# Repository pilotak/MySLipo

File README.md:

# MySensors Li-po/USB powered wirelles node

PCB size as 18500 Li-po battery board with ATmega328p with integrated USB charger and battery protection IC. Supports ATSHA204A CryptoAuth chip, DS18B20 temperature IC and Meder reed switch.

### Power consumption
* sleep: 58.1uA
* wakeup: 18.2mA

### Supported radios:
* NRF24L01 SMD
* NRF24L01+LNA+PA SMD

### Pins used:
* D2 = reed switch 1
* D3 = reed switch 2
* D4 = 1-Wire bus with R2 pull-up to D5
* D5 = 1-Wire supply
* D7 = LED indication
* D9 = CE pin
* D10 = CSN
* SPI = radios
* A2 = ATSHA204A
* A7 = battery monitor

## PCB top view

## PCB bottom view

### ATmega328p fuses
- **HIGH:** DA
- **LOW:** E2
- **EXTENDED:** 06

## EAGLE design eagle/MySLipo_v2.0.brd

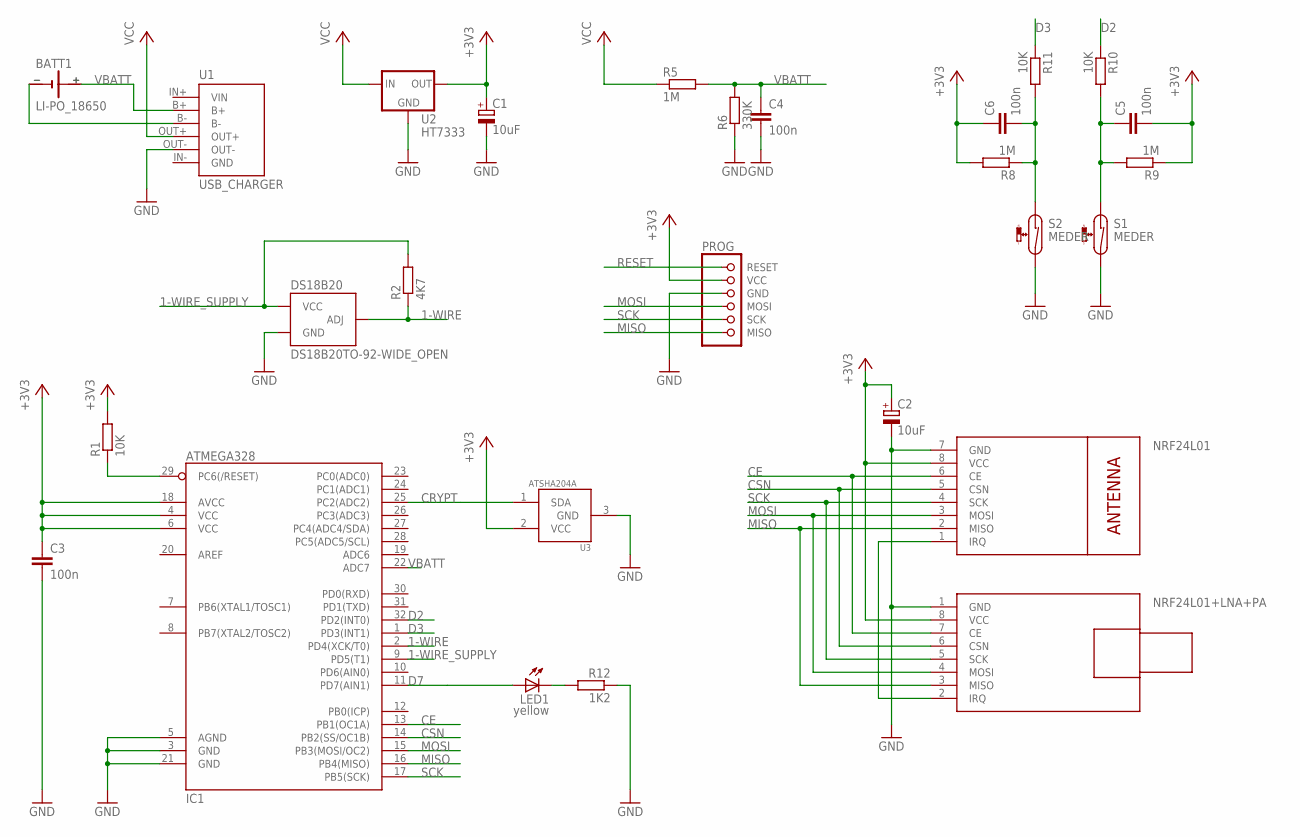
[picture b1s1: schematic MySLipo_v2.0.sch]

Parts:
BATT1: LI-PO_18650; 18650_HOLDER
C1, C2: 10uF; SMC_A
C3, C4, C5, C6: 100n; C0805
DS18B20: DS18B20TO-92-WIDE_OPEN; TO-92-WIDE_OPEN
IC1: ATMEGA328; TQFP32-08
LED1: yellow; LED_0805
NRF24L01: WIRELESS-NRF24L01SMD2; WIRELESS-NRF24L01-SMD-2
NRF24L01+LNA+PA: WIRELESS-NRF24L01-PA-EXTSMD; WIRELESS-NRF24L01-PA-SMD
PROG: PROG
R1, R10, R11: 10K; R0805
R2: 4K7; R0805
R5, R8, R9: 1M; R0805
R6: 330K; R0805
R12: 1K2; R0805
S1, S2: MEDER; 15X
U1: USB_CHARGER
U2: HT7333; SOT89
U3: ATSHA204A; SOT23-3

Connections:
1-WIRE: DS18B20.G (ADJ), IC1.2 (PD4(XCK/T0)), R2.1
1-WIRE_SUPPLY: DS18B20.S (VCC), IC1.9 (PD5(T1)), R2.2
+3V3: C1.+, C2.+, C3.1, C5.2, C6.1, IC1.4 (VCC), IC1.6 (VCC), IC1.18 (AVCC), NRF24L01.8 (VCC), NRF24L01+LNA+PA.8 (VCC), PROG.2 (VCC), R1.2, R8.2, R9.1, U2.3 (OUT), U3.2 (VCC)
CE: IC1.13 (PB1(OC1A)), NRF24L01.6 (CE), NRF24L01+LNA+PA.7 (CE)
CRYPT: IC1.25 (PC2(ADC2)), U3.1 (SDA)
CSN: IC1.14 (PB2(SS/OC1B)), NRF24L01.5 (CSN), NRF24L01+LNA+PA.6 (CSN)
D2: IC1.32 (PD2(INT0)), R10.1
D3: IC1.1 (PD3(INT1)), R11.1
D7: IC1.11 (PD7(AIN1)), LED1.1 (A)
GND: C1.-, C2.-, C3.2, C4.2, DS18B20.D (GND), IC1.3 (GND), IC1.5 (AGND), IC1.21 (GND), NRF24L01.7 (GND), NRF24L01+LNA+PA.1 (GND), PROG.3 (GND), R6.1, R12.1, S1.P$2 (2), S2.P$2 (2), U1.OUT-, U2.1 (GND), U3.3 (GND)
MISO: IC1.16 (PB4(MISO)), NRF24L01.2 (MISO), NRF24L01+LNA+PA.3 (MISO), PROG.6 (MISO)
MOSI: IC1.15 (PB3(MOSI/OC2)), NRF24L01.3 (MOSI), NRF24L01+LNA+PA.4 (MOSI), PROG.4 (MOSI)
unnamed: NRF24L01.1 (IRQ), NRF24L01+LNA+PA.2 (IRQ)
unnamed: C5.1, R9.2, R10.2, S1.P$1 (1)
unnamed: C6.2, R8.1, R11.2, S2.P$1 (1)
unnamed: BATT1.-, U1.B-
unnamed: LED1.2 (C), R12.2
RESET: IC1.29 (PC6(/RESET)), PROG.1 (RESET), R1.1
SCK: IC1.17 (PB5(SCK)), NRF24L01.4 (SCK), NRF24L01+LNA+PA.5 (SCK), PROG.5 (SCK)
VCC: R5.1, U1.OUT+, U2.2 (IN)

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
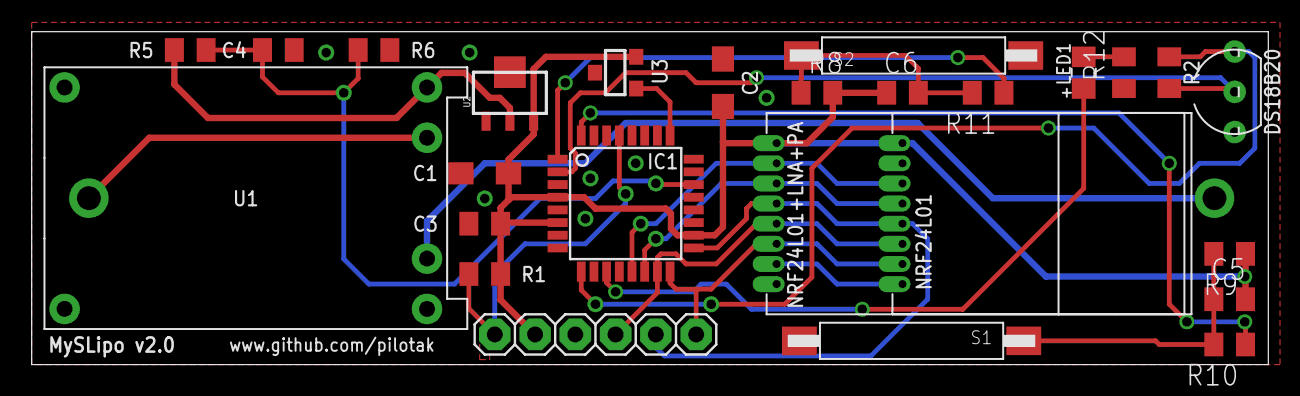
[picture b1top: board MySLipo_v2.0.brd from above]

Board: 2 copper layers, 78.0 x 21.0 mm, 27 parts (1 on the bottom side), 22 nets.

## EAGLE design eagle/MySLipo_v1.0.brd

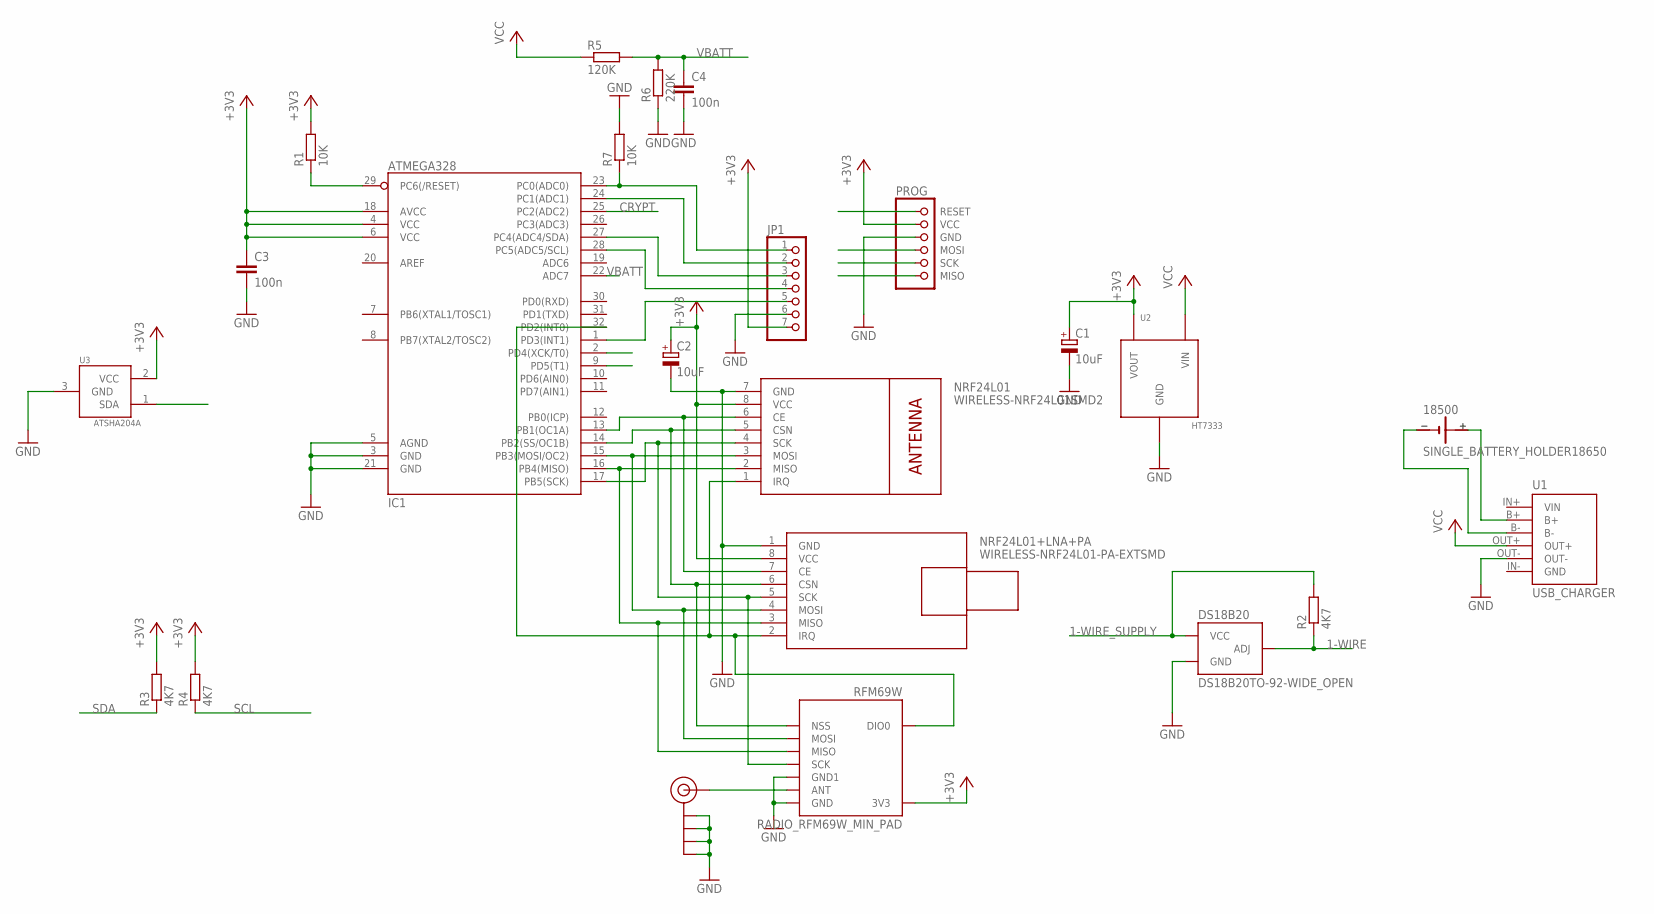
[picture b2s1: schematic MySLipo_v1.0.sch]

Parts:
18500: SINGLE_BATTERY_HOLDER18650; 18650_HOLDER
C1, C2: 10uF; SMC_A
C3, C4: 100n; C0805
DS18B20: DS18B20TO-92-WIDE_OPEN; TO-92-WIDE_OPEN
IC1: ATMEGA328; TQFP32-08
J$1: ANTENNATINY; SMA_UFL_PAD_TINY
JP1: PINHD-1X7; 1X07
NRF24L01: WIRELESS-NRF24L01SMD2; WIRELESS-NRF24L01-SMD-2
NRF24L01+LNA+PA: WIRELESS-NRF24L01-PA-EXTSMD; WIRELESS-NRF24L01-PA-SMD
PROG: PROG
R1, R7: 10K; R0805
R2, R3, R4: 4K7; R0805
R5: 120K; R0805
R6: 220K; R0805
RFM69W: RADIO_RFM69W_MIN_PAD; RFM69W_MIN_PAD
U1: USB_CHARGER
U2: HT7333; SOT-89
U3: ATSHA204A; SOT23-3

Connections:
1-WIRE: DS18B20.G (ADJ), IC1.2 (PD4(XCK/T0)), R2.1
1-WIRE_SUPPLY: DS18B20.D (VCC), IC1.9 (PD5(T1)), R2.2
+3V3: C1.+, C2.+, C3.1, IC1.4 (VCC), IC1.6 (VCC), IC1.18 (AVCC), JP1.7, NRF24L01.8 (VCC), NRF24L01+LNA+PA.8 (VCC), PROG.2 (VCC), R1.2, R3.2, R4.2, RFM69W.8 (3V3), U2.3 (VOUT), U3.2 (VCC)
A0: IC1.23 (PC0(ADC0)), JP1.1, R7.1
A1: IC1.24 (PC1(ADC1)), JP1.2
ANT: J$1.ANT1 (SIGNAL), J$1.ANT2 (SIGNAL), J$1.ANT3 (SIGNAL), RFM69W.10 (ANT)
CRYPT: IC1.25 (PC2(ADC2)), U3.1 (SDA)
D2: IC1.1 (PD3(INT1)), JP1.5
GND: C1.-, C2.-, C3.2, C4.2, DS18B20.S (GND), IC1.3 (GND), IC1.5 (AGND), IC1.21 (GND), J$1.GND1 (GND), J$1.GND2 (GND), J$1.GND3 (GND), J$1.GND4 (GND), JP1.6, NRF24L01.7 (GND), NRF24L01+LNA+PA.1 (GND), PROG.3 (GND), R6.1, R7.2, RFM69W.9 (GND), RFM69W.11 (GND1), U1.OUT-, U2.1 (GND), U3.3 (GND)
MISO: IC1.16 (PB4(MISO)), NRF24L01.2 (MISO), NRF24L01+LNA+PA.3 (MISO), PROG.6 (MISO), RFM69W.13 (MISO)
MOSI: IC1.15 (PB3(MOSI/OC2)), NRF24L01.3 (MOSI), NRF24L01+LNA+PA.4 (MOSI), PROG.4 (MOSI), RFM69W.14 (MOSI)
unnamed: IC1.32 (PD2(INT0)), NRF24L01.1 (IRQ), NRF24L01+LNA+PA.2 (IRQ), RFM69W.2 (DIO0)
unnamed: IC1.13 (PB1(OC1A)), NRF24L01.6 (CE), NRF24L01+LNA+PA.7 (CE)
unnamed: IC1.14 (PB2(SS/OC1B)), NRF24L01.5 (CSN), NRF24L01+LNA+PA.6 (CSN), RFM69W.15 (NSS)
unnamed: 18500.+, U1.B+
unnamed: 18500.-, U1.B-
RESET: IC1.29 (PC6(/RESET)), PROG.1 (RESET), R1.1
SCK: IC1.17 (PB5(SCK)), NRF24L01.4 (SCK), NRF24L01+LNA+PA.5 (SCK), PROG.5 (SCK), RFM69W.12 (SCK)
SCL: IC1.28 (PC5(ADC5/SCL)), JP1.4, R4.1
SDA: IC1.27 (PC4(ADC4/SDA)), JP1.3, R3.1
VBATT: C4.1, IC1.22 (ADC7), R5.2, R6.2
VCC: R5.1, U1.OUT+, U2.2 (VIN), U2.2@1 (VIN)

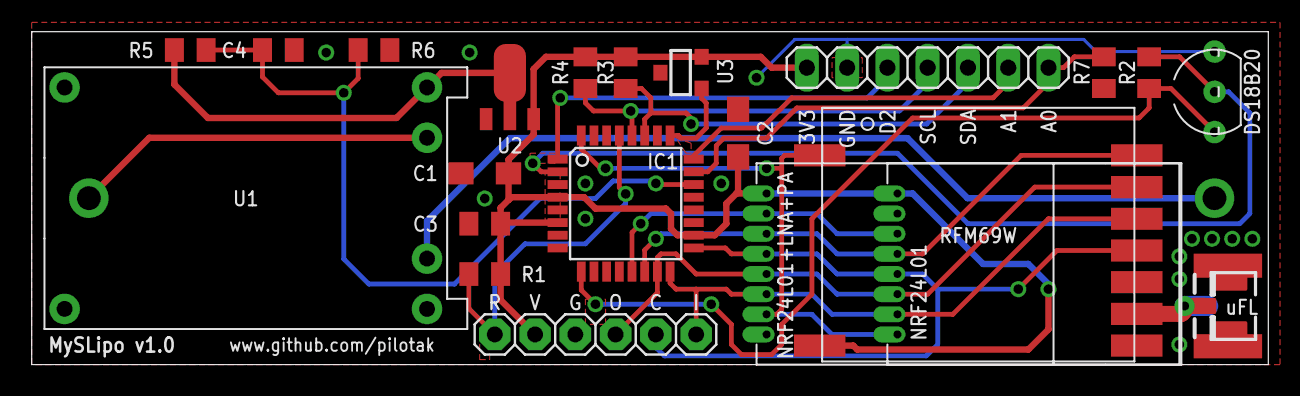
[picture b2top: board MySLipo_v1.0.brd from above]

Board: 2 copper layers, 78.0 x 21.0 mm, 23 parts (1 on the bottom side), 22 nets.

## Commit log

2016-12-27 src files
2016-12-27 readme update
2017-02-22 INO file upload
2017-02-24 power consumption info
2017-09-06 v2.0
2017-09-11 LED added to FW
2018-12-29 moved to PlatformIO
2018-12-30 v1.0.0
2018-12-30 docu update
    [ci skip]
2018-12-30 eagle update
2018-12-30 img update
    [ci skip]
2020-08-16 folder restructure
2020-08-16 moved from Travis to GithubCI
2020-08-16 CI update
2020-09-24 CI split build & release
